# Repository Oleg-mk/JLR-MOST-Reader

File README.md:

# JLR MOST Reader

A listen-only adapter for the MOST25 optical ring in Jaguar and Land Rover cars. It takes the stereo
the head unit sends to the factory amplifier and outputs it as S/PDIF on a TOSLINK socket, for an
aftermarket DSP or amplifier. On MOST that audio travels round the ring in channels any node can
read, so the reader can hear exactly what the amplifier plays.
**The car's own volume knob and steering-wheel buttons keep working: the reader applies their level
digitally, with no loss of quality** ([how](#volume-from-the-cars-own-controls-with-no-loss-of-quality)).
It can also log everything it sees on the ring to a laptop over USB.

**Status, 2026-10-11: designed and verified in simulation, but never built and never tried in a
car.** The author can't build it locally, so the whole design is published here for anyone who can.
Every file you need to order, flash and assemble one is in this repository.

**This is a research project.** Every finding, recording, correction or bit of help is welcome
and will go into the project: open an issue or a pull request, or write in the forum thread.

Ukrainian: [README.uk.md](README.uk.md).

## Volume from the car's own controls, with no loss of quality

The audio on the ring travels before the volume: the factory amplifier applies volume and tone
itself. A plain MOST-to-TOSLINK tap would therefore play at full level, whatever the knob says.
The reader decodes the volume messages and applies the level itself, in the digital domain.

- **The stock controls keep working.** The knob and the steering-wheel buttons set the level as
  before. Navigation prompts and phone calls are mixed in at their own levels, and a Mute
  (0x22.0x113) is applied.
- **Nothing is lost on the way:**
  - the 16-bit stereo is taken straight from the ring's frames, sample for sample;
  - the level is applied in 32-bit arithmetic (a 72-bit accumulator) and rounded once, to the
    24-bit output. Every bit of the 16-bit source survives down to 48 dB of attenuation, and the
    rounding sits at the 24-bit level, about 144 dB below full scale;
  - no resampling: the S/PDIF runs at the ring's own 48 kHz, one output frame per ring frame;
  - no DAC or ADC in between: the sound stays digital until your DSP or amplifier.
- **Level changes are smooth:** a new level settles in about 5 ms, without clicks.

Your DSP or amplifier can then run at a fixed gain, and the car's controls do the rest. One thing
is still open: if the XF's amplifier turns out to get the gateway's 0x409 levels rather than
SpeakerLevel in dB, their raw-to-dB curve has to be measured from a recording (see
[Status](#status-what-is-proved-and-what-is-not)).

## What it does

- **Not an amplifier emulator.** An emulator takes the factory amplifier's place on the ring and
  answers the head unit as the amplifier. This reader takes no place on the network: the factory
  amplifier stays in the ring and keeps working, and the reader reads the same audio channels the
  amplifier plays and processes them. In effect it is a MOST bus sniffer with an audio path.
- **Sits in the ring like any MOST device:** fibre in, fibre out. A loop-in adapter cable opens the
  ring at an existing node's connector.
- **Decodes the control channel:** Connect and DisConnect to the amplifier (FBlock 0x22
  AudioAmplifier; on the XF node 0x186, instance 0x05, but any node and instance is taken, see
  [Status](#status-what-is-proved-and-what-is-not)), SinkInfo, Mute, and the two volume messages
  seen so far (0x22.0x46D SpeakerLevel in dB, and the gateway's 0xF0.0x409 levels).
- **Plays four streams from the frames,** at the positions the Connect messages give: the main
  source; phone, navigation and voice prompts; the parking sensors; the chimes. These are the
  amplifier's sinks 1 to 4 as JLR uses them. Each stream gets its own level and mute: the
  parking sensors follow their own level setting, and the chimes keep a fixed level, so they can't
  disappear with the volume turned down.
- **Outputs S/PDIF:** 24-bit, at the ring's 48 kHz, IEC 60958-3 consumer format, through an
  Everlight T10 TOSLINK transmitter.
- **Logs to a laptop:** what it receives and what it decides, through the Tang Nano's USB-UART.
  The laptop tools (Python, Windows 10/11 and macOS) record a drive and decode it at home.
- **Never transmits on MOST** and has no address.

Hardware: a Sipeed Tang Nano 20K FPGA module (GW2AR-18) on a small carrier board, with a TE MOST FOT
header, power from the car's permanent 12 V (KL30), and a TOSLINK transmitter. The gateware runs on
one clock and replaces both the MOST chip and the host CPU that a design like this usually needs.

## Which cars

- **Target:** Jaguar XF X250 (2008-2015). The messages it decodes are the ones open projects
  recorded on JLR cars (see [SOURCES.md](SOURCES.md)).
- **What the car must have:** a MOST25 ring at 48 kHz, and a separate amplifier that gets its audio
  over that ring. The amplifier stays in place: the head unit sends the audio to it, and the reader
  finds that audio from the Connect messages addressed to the amplifier.
- **Not the standard audio.** In cars where the head unit's own amplifier drives the speakers (the
  XF's standard audio), no audio for an amplifier travels the ring, so the reader has nothing to
  take. Switching the car's configuration from premium to standard stops that audio (a forum
  member with SDD), and mObridge's guide asks for the car to be coded when the factory MOST
  amplifier is missing ([SOURCES.md](SOURCES.md)).
- **Other cars:** other JLR models of the same generation with the same setup are candidates;
  Freelander 2 is the one with published evidence. Volume messages differ between models, and the
  logger exists to find that out.
- **Not other makes:** the Audi and BMW systems surveyed run their rings at 44.1 kHz and use
  different control messages.

## Is it safe for the car's ring?

The part that stays in the ring is small and separate from everything else:

```
ring in -> FOT receiver -> R1 -> U1 (one 74LVC1G34 buffer) -> R2 -> FOT transmitter -> ring out
```

- **The bypass:** U1 and the FOT run from their own 3.3 V regulator (TPS7B8133). It is fed from
  KL30 through the board's 12 V input (the fuse F1, the diode D1, the filter L2) and is always on,
  drawing tens of microamps with the car parked (the design figure; not yet measured). Nothing
  switches this path. It drives the transmitter the same way a powered OS8104 node in all-bypass
  does after reset.
- **Everything else is off the light path:** the FPGA module, its 5 V buck converter (switched on
  by light arriving on the ring), the gateware and the TOSLINK output. If the module, the gateware
  or the output fails, the ring still passes light. The FPGA's input is isolated by a 74LVC1G125
  with Ioff, so an unpowered module doesn't load the line.
- **When the ring opens:**
  - the bypass loses its supply: KL30 disconnected, or your fuse or F1 blown;
  - a part on the board's 12 V input fails: the bypass shares that input with the buck, so a
    short there (the buck's input, a capacitor on the 12 V side, D2) blows F1, and an open F1, D1
    or L2 cuts the supply;
  - a part on the light path fails: J1's FOT, R1, U1, R2 (and R43 on v2.0), or the 3.3 V
    regulator.

  The same is true of every factory MOST node that loses its supply. Fit your own fuse where you
  tap KL30.
- **Nothing new on the network:** the reader sends nothing on MOST and has no address, so the car's
  network sees no new node.
- **Fully reversible:** unplug the loop-in adapter and the car is back to stock.
- **Start-up volume:** until the first volume message arrives, the main source plays at -12 dB, and
  phone/navigation, the parking sensors and the chimes at -6 dB. Keep your DSP's or amplifier's own gain low on the
  first drive.

## The factory amplifier

The reader only listens, so the factory amplifier stays in the ring, powered, and keeps playing.
That is the price of not emulating it, and it decides how you use the output.

- **Add to the stock system:** a subwoofer, a second amplifier, a DSP for extra speakers. Nothing
  in the car changes.
- **Take the factory speakers over:** your amplifier, fed by the reader, drives the factory
  speakers, and the factory amplifier is left without them.
  - **Fault codes:** it tests its speaker lines, so expect speaker-open codes in it. An XKR owner
    who did exactly this with a commercial MOST interface reports codes for the amplifier and
    every speaker that come back after clearing ([SOURCES.md](SOURCES.md)).
  - **Anything beyond the codes** is still being looked into. Findings are welcome.
  - **The service sounds:** per mObridge's guide, JLR sends the phone, navigation and voice prompts
    (sink 2), the parking sensors (sink 3) and the chimes (sink 4) to the amplifier over the ring
    as audio. The reader plays all of them, so moving the speakers loses none. The first
    recording will confirm it: the trip instructions ask for a mark at reverse gear and at every
    chime.

**Can the reader replace the factory amplifier? No.**
- **Nobody answers for it.** The reader has no address and sends nothing, by hardware: the ring's
  transmitter is driven by one buffer, and the FPGA has no way onto it. With the amplifier gone,
  nobody answers as node 0x186 / FBlock 0x22.
- **The car needs it.** An XF owner who bypassed the amplifier with a fibre loop reports the screen
  stuck on the logo and no sound ([SOURCES.md](SOURCES.md)).
- **That is an emulator's job.** Taking the amplifier's place means transmitting on MOST.
- **It must stay powered.** Without power its own bypass goes dark and the ring opens.

## Status: what is proved and what is not

**Verified in models** (run `python check_all.py`; every step passes):

- The gateware, in Icarus Verilog against bit-exact Python models:
  - the control decoder, through five scenarios and 400 random blocks;
  - the frame timing at +-1000 ppm with jitter;
  - the DSP and the S/PDIF line, read back and decoded;
  - the whole reader from the optical line: a modelled JLR ring distorted to the edge of the MOST25
    receiver limits (SP4), through to the S/PDIF output;
  - the ring log, record by record, as far as the laptop's parser.
- The Gowin build meets timing with at least 10 % margin; the bitstream in `kit/2_fpga` was built
  from the committed sources.
- The boards:
  - KiCad ERC and DRC clean, with parity between schematic and board;
  - the v2.0 netlist compared with v1.0 part by part and net by net;
  - the board's fit in the tube and the end caps, all generated from one model (`reader_hw2/check_fit.py`).
- The decoder and the gain tables, cross-checked against C code written separately in the author's
  earlier project, [MOST25-to-AUDIO](https://github.com/Oleg-mk/MOST25-to-AUDIO).

**Unknown until a bench or a car:**

- **Volume message:** which one the XF's amplifier actually gets. Both are decoded. JLR-HU's
  table of the amplifier's own functions lists 0x46D SpeakerLevel and not 0x400 Volume: a point
  for 0x46D.
- **Connect:** whether the stock head unit sends 0x22.0x111 Connect at all.
- **The 0x409 levels:** JLR-HU's author has read them two ways; the later one is used (the volume
  in byte 2, the navigation in byte 9, the parking sensors in byte 11). The level curves are
  placeholders.
- **Mute:** whether JLR mutes with 0x113 Mute, which is decoded, or with 0x466 MuteParameters,
  which is not (usb2most's firmware mutes with 0x466).
- **MixerLevel:** 0x22.0x467 is not decoded. It is not among the amplifier's own functions in
  JLR-HU's table and is taken to belong to the gateway's shadow amplifier (below).
- **The gateway's shadow amplifier,** 0x22 instance 0xA1 at node 0x161: the reader does not tell
  it apart from the amplifier, so a Connect or a Mute sent to it would act on the reader's streams.
- **Real hardware:** how a real S/PDIF receiver locks to the output's edges, which sit on a
  1.26 ns grid, and whether the module's USB bridge sustains 3 Mbaud into Windows.

The log is designed to answer these on the first drive ([reader_gw/README.md](reader_gw/README.md),
[reader_gw/LOGGING.md](reader_gw/LOGGING.md)).

## Build one

The short version is below; the full guide is [BUILD.md](BUILD.md). There are two boards with the
same circuit. **v2.0** (`reader_hw2/`) is the one to build:
84.9 x 26.5 mm, two layers, inside a 30 x 30 x 1.5 mm aluminium tube with two 3D-printed end caps.
v1.0 (`reader_hw/`) is a flat 77.5 x 55.6 mm board with mounting holes.

1. **Measure first.** The end caps depend on the tube's inside (27.0 mm nominal), how far the
   module's HDMI and USB-C stick out past its board (4 and 2 mm assumed), and J4's tail length
   (3.0 mm assumed). The list is in `reader_hw2/kit/1_boards/README.md`, "Перед замовленням виміряти".
2. **Order the boards** from JLCPCB. Everything is in `reader_hw2/fab/`.
   - Board: `most_reader_v2-gerbers.zip`. 2 layers, 1.6 mm, 1 oz, ENIG; U4, U5 and U6 need flat pads.
   - Assembly: the bottom side only, with `most_reader_v2-bom-jlcpcb.csv` and
     `most_reader_v2-cpl-jlcpcb.csv`. That is 30 lines and 52 parts, every one with its LCSC number.
   - In their placement preview, check pin 1 of U1, U3, U4, U5 and U6, and the polarity of D1, D2,
     D3, C44, C45 and C63.
3. **Buy the hand-soldered parts:**

   | Ref | Part | Note |
   |---|---|---|
   | J1 | TE 1-1394640-1, MOST pigtail FOT header (2+0) | not stocked by Mouser or DigiKey; marketplaces only, look early |
   | J4 | Molex 43650-0200, Micro-Fit 3.0 right angle; mating 43645-0200 and two 43030 terminals | 12 V from KL30 |
   | J6 | Everlight PLT237/T10WH | DigiKey 1080-PLT237/T10WH-ND |
   | M1 | Sipeed Tang Nano 20K | with its pin headers, cut to nine pins |

   You also need:
   - a 30 x 30 x 1.5 aluminium tube, 84.9 mm (+0.2/-0) long, best left bare;
   - two M2 x 6 self-tapping screws, an M2 ring terminal and a serrated washer for the tube's ground;
   - four 4.2 mm self-tapping screws (DIN 7981) or M4 screws to fix it in the car;
   - a MOST loop-in adapter for the node you will tap, as made by Kufatec, Dension or Trioma;
   - a TOSLINK cable.
4. **Flash the FPGA** before soldering the module: write `kit/2_fpga/reader.fs` to its flash. On
   Windows use Gowin Programmer; on macOS, `openFPGALoader -b tangnano20k -f --verify reader.fs`.
   The module's BL616 bridge needs firmware 2025030317 or newer (`kit/2_fpga/README.md`).
5. **Solder:**
   - J6 and J4 from below, with their leads cut flush where the module will sit;
   - J1 on top at the ring edge;
   - M1 last, on nine header pins only: 5, 7, 8, 20 and 21, 22, 25, 35, 40. Cut the strips into
     pieces (5 | 7-8 | 20 and 21-22 | 25 | 35 | 40) and let the board hold them square.
6. **Bench:**
   - Check for shorts across J4, C3 and C63, then power from a current-limited 12 V supply.
     C3 shows 3.3 V at all times.
   - With light into J1, C63 shows about 5.3 V and the module starts.
   - Then record on the bench with the laptop tools (`kit/3_laptop/`).
7. **Tube:**
   - Print the caps from `reader_hw2/caps/` in PETG or ASA. The drawing is
     [caps_en.svg](reader_hw2/caps/caps_en.svg).
   - Fit the far cap, slide the board in from the ring end until it meets the far cap, then fit
     the ring cap; one screw each.
   - Run a short wire from the far cap's screw to J4's ground at the plug.
   - Each cap runs on under the tube into a saddle with an ear on either side. The tube's floor
     rests on the two saddles, and four screws through the ears hold the reader in the car.
8. **Car:**
   - First the bypass alone: the reader in the ring, powered, and the car must sound exactly as before.
   - Then a drive with the log running.

**The full step-by-step guide in English is [BUILD.md](BUILD.md).** The same instructions in
Ukrainian are the kit's: [reader_hw2/kit/README.md](reader_hw2/kit/README.md),
[reader_hw2/kit/1_boards/README.md](reader_hw2/kit/1_boards/README.md),
[kit/2_fpga/README.md](kit/2_fpga/README.md) and [kit/3_laptop/README.md](kit/3_laptop/README.md).
The board and its design choices are described in [reader_hw2/README.md](reader_hw2/README.md).

## Rough cost

| Item | Approx. USD | Basis |
|---|---|---|
| JLCPCB: 5 boards, 2 of them assembled | 60-100, plus shipping and tax | their price page, seen 2026-10-12 (updated 2026-09-09): Economic PCBA (one side, as here): $8.18 setup, $1.53 stencil and $3.07 per extended part type (about 15 here), plus the parts and the ENIG boards |
| Sipeed Tang Nano 20K | 25-35 | $25 at launch; resellers $27-36 |
| TE 1-1394640-1 (J1) | 22-27, plus shipping | no distributor stocks it; eBay about $22 (2026-10-12), AliExpress about $27 (2026-10-13) |
| T10 transmitter, Micro-Fit pair, tube, printed caps, screws, a fuse and wire for the 12 V tap | 15-25 | rough |
| MOST loop-in adapter, TOSLINK cable | 25-60 | rough; depends on the node you tap |

The first reader comes to roughly $150-250, plus shipping and tax. A second reader from the same
order needs no new boards: about $90-150 for its module, J1, the other hand parts, the tube and
the cables.

## Repository map

| Path | What |
|---|---|
| `reader_hw2/` | **v2.0 board** (KiCad 10): generators, the board, `fab/` for JLCPCB, `caps/` for the tube, `views/` pictures, `kit/` instructions |
| `reader_hw/` | v1.0 board, same circuit, flat with mounting holes |
| `reader_gw/` | gateware for the Tang Nano 20K: RTL, simulations, the Gowin build |
| `kit/` | what a builder takes away: v1.0 fab files, the bitstream, the laptop tools |
| `virtual_most_source/` | a Python model of a MOST25 ring and of JLR's messages, which the simulations use |
| `tools/` | checks: sheet, board, pins, cross-checks, the kit's builder, the laptop's logger and decoder |
| `check_all.py` | every check in turn |

Tools: KiCad 10, Python 3, OSS CAD Suite (Icarus Verilog) for the simulations, and Gowin EDA
1.9.12.03 to rebuild the bitstream (the committed one is ready to flash). Two cross-check steps
need the author's earlier project, [MOST25-to-AUDIO](https://github.com/Oleg-mk/MOST25-to-AUDIO),
cloned next to this one, and a host gcc; without them they fail ([SOURCES.md](SOURCES.md)).

## Licence

Copyright 2026 Oleg-mk.

- **Hardware, under CERN-OHL-S-2.0** ([LICENSE](LICENSE)):
  - `reader_hw/`, `reader_hw2/` (the KiCad design and the scripts that generate it, footprints,
    3D models, fabrication files, end caps);
  - the gateware in `reader_gw/rtl/` and `reader_gw/board/`;
  - `kit/1_boards/` and `kit/2_fpga/`.
- **Software, under GPL-3.0-or-later** ([COPYING](COPYING)):
  `virtual_most_source/`, `tools/`, `reader_gw/sim/`, `kit/3_laptop/` and `check_all.py`.
- **Documentation:** each README and drawing is under the licence of the directory it sits in.

If you build or change the hardware and share it, share your sources under the same licence.

## How it was made

The author made the decisions and placed the parts. Claude (Anthropic's AI model,
in Claude Code) wrote the gateware, the models and simulations, the board generators and copper,
and the checks, as a co-author. The commit history shows both.

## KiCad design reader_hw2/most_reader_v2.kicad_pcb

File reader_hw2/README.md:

# reader_hw2 - reader v2.0: v1.0's circuit plus two resistors, a board for a tube

v2.0 is v1.0's electronics, plus two series resistors (R43, R44, below) and a smaller C45, on a board that slides
into a square aluminium tube with two end caps: a 30x30x1.5 tube (27.0 inside), a board 26.5 mm
wide, the module's own USB-C in the far end cap with no extension cable. v1.0 (`reader_hw`) is
not touched.

```text
python reader_hw2/gen_reader2.py               the sheet, the libraries, the footprints, the 3D bodies
"%LOCALAPPDATA%\Programs\KiCad\10.0\bin\python.exe" reader_hw2\gen_reader2_pcb.py [--fresh]
                                               the first placement (refuses to overwrite without --fresh)
"%LOCALAPPDATA%\Programs\KiCad\10.0\bin\python.exe" reader_hw2\check_fit.py
                                               the board in the tube: heights, corners, leads, the caps
python tools/check_v2_circuit.py               v2.0's circuit equals v1.0's once R43, R44 are shorted
python tools/check_board.py reader_hw2/most_reader_v2.kicad_pcb
                                               DRC with the parity check, the silkscreen minimums
python reader_hw2/make_fab.py                  the manufacturing package in fab/: JLCPCB, SMD on the bottom
"%LOCALAPPDATA%\Programs\KiCad\10.0\bin\python.exe" reader_hw2\gen_caps.py
                                               the tube's end caps in caps/: STEP, STL, the drawing
python tools/make_kit.py --v2 DIR              the kit in DIR: 1_boards, 2_fpga, 3_laptop (READMEs in kit/)
```

All but the last run in `check_all.py`.

## The sheet

`gen_reader2.py` does not draw the circuit again: it loads `reader_hw/gen_reader.py` and writes
its blocks 1-7 into this folder, under the project name `most_reader_v2` with its own UUIDs. It
changes what describes the board and adds two resistors:

- the title block (rev 2.0) and two lines of notes;
- the Tang Nano footprint: nine pads only, 5, 7, 8, 20 and 21, 22, 25, 35, 40: the
  seven that carry something and one at each corner they leave bare. The strips are cut to them
  (pieces of one and two pins), and the rows of holes under the module are free for tracks; pins
  1..4 would sit over J4 on the other side anyway. KiCad's parity check asks no pad of an
  unconnected pin.
  The footprint also draws the module's real overhangs (USB-C 2 mm, HDMI about 4 mm; v1.0's fab
  text says 8 mm, which was never measured) and carries a 3D body of the module;
- the FOT footprint's two action pins: rings of 2.1 mm instead of 2.4, so that their copper keeps
  0.3 mm from the long edges of the 26.5 mm board (their 1.8 mm holes sit 0.5 mm from them);
- R43 (33 ohm) and R44 (68 ohm) in series right after U1 (RX_BUF) and U3 (RX_IN): on two layers
  those lines run about 40 and 60 mm as 100-130 ohm lines with ~1 ns LVC edges. A model of RX_IN
  (the line, U3 at 15-25 ohm, the FPGA pin 6-8 pF) gives 13-31 % overshoot with 33 ohm and at
  most 8 % with 68, the edge 1.0-1.6 ns, which the decoder does not mind. R43 stays 33: RX_BUF
  also drives the ring's TX through R2, where a fast edge matters more.
- C45 47u 63V in 8 x 10 instead of 100u in 10 x 10.5. The bulk capacitance on
  VBAT_P drops from 200 to 147 uF, 9.6 times the 15.3 uF of ceramics there (13 before): still
  enough to damp the harness against them.

`tools/check_v2_circuit.py` compares both sheets' netlists with R43 and R44 shorted out and C45's
one change allowed: 58 parts, 63 nets, no other difference.
Since `tools/check_pins.py` holds v1.0's sheet to the gateware's `.cst`, the gateware and the
bitstream in `kit/2_fpga` hold for v2.0 unchanged.

## Why 26.5 mm and 1.5 mm walls

Both come from J1, not from the module:

- **Width.** J1's housing is 25.5 mm wide (TE's view drawing C-2-2141577-1), and its two action
  pins stand in 1.8 mm holes whose outer edges are 25.5 mm apart. A 26 mm board would leave
  0.25 mm of FR-4 outside each hole.
- **Height.** J1 stands 13.25 mm above the board, more than the module's 10.1. With the board and
  C44 underneath (10.5 + 0.3): 13.25 + 1.6 + 10.8 = 25.65 mm. A 2 mm wall (26 inside) leaves
  0.35 mm for everything; 1.5 mm (27 inside) leaves 1.35: 0.5 above J1, 0.5 under C44, and the
  window for the board's height.

## The layout

26.5 x 84.9 mm, two layers. x runs along the tube from the ring's end (0) to the far end (84.9).

| Side | Where | What |
|---|---|---|
| top | ring end | J1, its foot on the edge, its housing 3.6 mm past it |
| top | x 31..85 | M1 along the tube, its USB-C on the far edge (2 mm past it, into the cap's cut-out) |
| bottom | under J1, x 10..22 | the FOT's supply filters on J1's pins; U4 with its RC; R1, U1 and R43 at RXD, R2 at TXD |
| bottom | x 21..37 | U5 with C46 and C3 behind J1; the bulk capacitor C44 with C47; U3 and R44 (/WAKE between its pads) |
| bottom | x 34..58 | U6 with C4, C82, C2, R31, C6 and the divider R4, R5; L1 and C7 for 5V_SW; C45, C43, C1, C84 on the VBAT_P bus |
| bottom | x 54..76 | the input from J4: L2, D1, D2, F1, C83; at the module's 5 V pin C63, C85, D3; R28, C31, C32 for J6 |
| bottom | far end | J4 (power) under the module's pins 1..4, J6 (TOSLINK) beside it |

Nothing but J1 and M1 is on top: the module's own parts (DC-DC, LDOs, crystals, the microSD slot)
fill the 2.5 mm under it.

Two lines run long, each from a buffer through a series resistor right after it: RX_IN from U3
through R44 (68 ohm) to the FPGA's pin 27 (module pad 8), 40 mm, and RX_BUF from U1 through R43
(33 ohm) to U3, R2 and U4, 20, 29 and 32 mm. VBAT_P comes from J4 through L2 along the bus at y 11
(C1, C43, C45) to U6's input caps and on to C44 and U5; /WAKE runs from U4 to U6, 3V3_SW from pad 7
to J6 and back along the bottom edge to U3.

**The length.** 84.9 mm. The module's end stays on the far edge, its HDMI 5.65 mm clear of J1.

## The model: check_fit.py

Every part is a box: its courtyard on the board and its height from a table with the source of
each number. The checks:

1. the board in the tube, at least 0.2 mm a side (0.25 now);
2. the tallest part on top plus the board plus the tallest underneath, with 0.5 mm above and
   below: the board's underside may sit 11.30..11.65 mm above the tube's floor, and goes at 11.47
   (the caps' slot); a tube 0.35 mm smaller inside still fits;
3. no box corner outside the tube's inside with its corners rounded by up to 1.0 mm (J1's housing
   is 1.10 and 0.40 mm from the walls, 0.68 under the top);
4. leads: J1's pins, legs and pegs land on no part underneath; no part underneath covers a pad
   of the module's header (its pins are soldered from underneath); J6's and J4's leads do not
   come up under J1 (it sits 0.45 mm above the board); under the module they are listed, to be
   cut flush;
5. the ends, with caps 2.0 mm thick: J1's housing 1.6 mm out of the ring cap; the USB-C's face on
   the far cap's outer face (0.06 inside); J6's port 0.29 out; J4's face 2.06 inside; the HDMI
   5.65 mm clear of J1.

It prints the caps' cut-outs (y from the left inside wall as seen from outside that end, z from
the tube's floor, mm), today:

| Cap | Cut-out | y | z |
|---|---|---|---|
| ring | J1's housing | 1.10..26.60 | 13.52..26.32 (the port sleeve's axis 19.92) |
| far | USB-C centre (receptacle 8.94 x 3.26) | 13.50 | 18.80 |
| far | J6's port axis | 9.50 | 7.12 |
| far | J4's face | 15.25..24.85 | 5.40..11.47 |

Planted faults (C44 over J1's peg, a part over a header pad, J6 under J1) each fail the check.

## Before the boards are ordered: measure

The model's weak numbers, in the order they matter:

- the tube's inside (27.0 nominal) and its corner radius;
- the module: how far the HDMI and the USB-C stand past its PCB, and the tallest part on its
  underside near the USB-C end (J6's and J4's cut leads sit there; 2.0 mm assumed);
- J4's tail and peg length under its seating plane (3.0 assumed);
- the caps' thickness at the cut-outs (2.0 assumed): the module's USB-C must end on the far cap's
  outer face.

## Assembly

1. JLCPCB places every SMD part, on the bottom.
2. J6 and J4 from the bottom, soldered on top; their leads (and J4's peg) cut flush where the
   module will sit.
3. J1 on top, soldered underneath.
4. The module on nine pins: the strips cut into pieces (5 | 7-8 | 20 and 21-22 | 25 | 35 | 40),
   put into the board, the module on top, soldered to the module first (the board holds them
   square), then underneath.

## Routing by hand

The board file is the master: `gen_reader2_pcb.py --fresh` would throw the copper away. The top is
the ground plane; underneath:

- the power section: C6 between U6 and L1, the SW node 3.7 mm, C4 straight onto U6's VIN and
  exposed pad; C45 8 mm across, on the bus by U6;
- the module's header cut to nine pins; the freed rows carry RX_IN and 3V3_SW;
- the far end: D3 lying, SPDIF between its pads; 3V3_SW from pin 7 between F1's and R28's pads to
  C31, C32 and J6, and from J6 down to the line under the module;
- /WAKE and RX_BUF straight across, from the top edge to their runs at x 25.5 and 25.05.

496 mm of copper, 75 vias; on the top only two jumpers, RX_IN over the C44 link (1.65 mm) and
VBAT_P over RX_BUF and /WAKE (1.75 mm); the top pour in one piece. DRC 0, no difference from the
sheet, nothing unconnected; no track runs over a pad of its own net without ending in it, no via
sits in a pad, no bend is acute. The series resistors' value depends on the line's impedance, not
on its length.

The sheet's test points TP6, TP7, TP9, TP10 are not on the board; the kit measures on C3
(3V3_AON), C63 (5V_SW) and the module's pin 7 (3V3_SW).

## The manufacturing package and the kit

`make_fab.py` writes `fab/` with v1.0's code: the Gerbers (the bottom paste, both silkscreens), the
BOMs and JLCPCB's CPL for the bottom side, the schematic and two assembly drawings (the bottom seen
from below, the top). A bottom part's rotation for JLCPCB is the angle at which it is seen from
below, 180 minus KiCad's, plus the part's own turn from v1.0's table; checked against the pads of
all 52 parts. `tools/make_kit.py --v2 DIR` writes the kit: 1_boards from `fab/` with the README in
`kit/1_boards`, the README in `kit/`, and v1.0's 2_fpga and 3_laptop.

## The end caps: gen_caps.py

The caps come from `check_fit.py`'s model (it must pass) and the board's leads, into `caps/`: a STEP
and an STL of each (the print's frame: the outer face on the bed), `caps.svg` (each cap seen from
outside, in section and from below, the sizes, the notes; `caps_en.svg` the same in English) and a
README.

- A flange of the tube's outline, 30 mm square and 2.0 mm thick, sits on the tube's end face; the
  board's ends butt against the flanges, so the tube is 84.9 mm (+0.2/-0), as long as the board.
- Every opening is its part plus 0.25 mm a side; no wall is thinner than 1.2 mm (three lines of a
  0.4 mm nozzle). J6's body and J4's face share one opening: the web between two would be 0.4 mm.
- The ring cap's block carries the board's underside at 11.47 mm and ends 1.0 mm before the first
  part underneath (8.5 mm into the tube); it stays 2.0 mm off J1's soldered action pins, and a slot
  along it, open to the inside, lets J1's peg through while the cap slides on under the board.
- The far cap's block sits over the module's end, 0.5 mm above the USB-C.
- Under the tube each flange runs on into a saddle:
  3.0 mm thick, 9.0 mm along the tube from its end, an ear 10.0 mm out on either side with a 4.2 mm
  hole. The tube's floor rests on the two saddles, and four screws through the ears hold the reader
  in the car: 4.2 mm self-tapping (DIN 7981) or M4, a head up to 8.2 mm clears the tube's side. The
  ring cap's saddle has a 5.0 mm hole round the head of the cap's own screw.
  - A tab past the tube's end would lie below the bed with the cap printed outer
    face down, and would need the cap on its side with supports under both blocks. At the far end it
    would also pass about 1 mm under a TOSLINK plug (J6's port axis 8.6 mm above the tube's bottom,
    a plug about 10 mm tall). The saddle rises from the bed with the flange: no supports, the ear
    holes horizontal.
- Each cap takes a self-tapping M2 screw through the tube's wall into its block, the hole in the
  block drilled at assembly: through the floor at the ring end, through the top at the far end.
- The tube is bonded to ground by J4 through the far cap's screw: an M2 ring terminal and a
  serrated washer under its head, a 3-5 cm wire to the GND wire of J4's harness by the plug. The
  board has no room for a bond there: the module's header rows run 2.2 mm from both long edges,
  J4 and J6 fill the end; the tube raw, or its anodizing scraped off under the washer.
- The script fails, writing nothing, when a wall comes out thinner, an opening closer to its part,
  a block onto a part or a lead, a saddle hole nearer an edge than 1.2 mm, or the mesh is open.
- `make_views.py` puts both caps and the tube on a copy of the board, point by point from the same
  solids, and renders the pictures in `views/` at basic quality: J1, the USB-C and J6 in their
  openings, the saddles under the tube.

## Not yet

The caps printed and tried on a real tube.

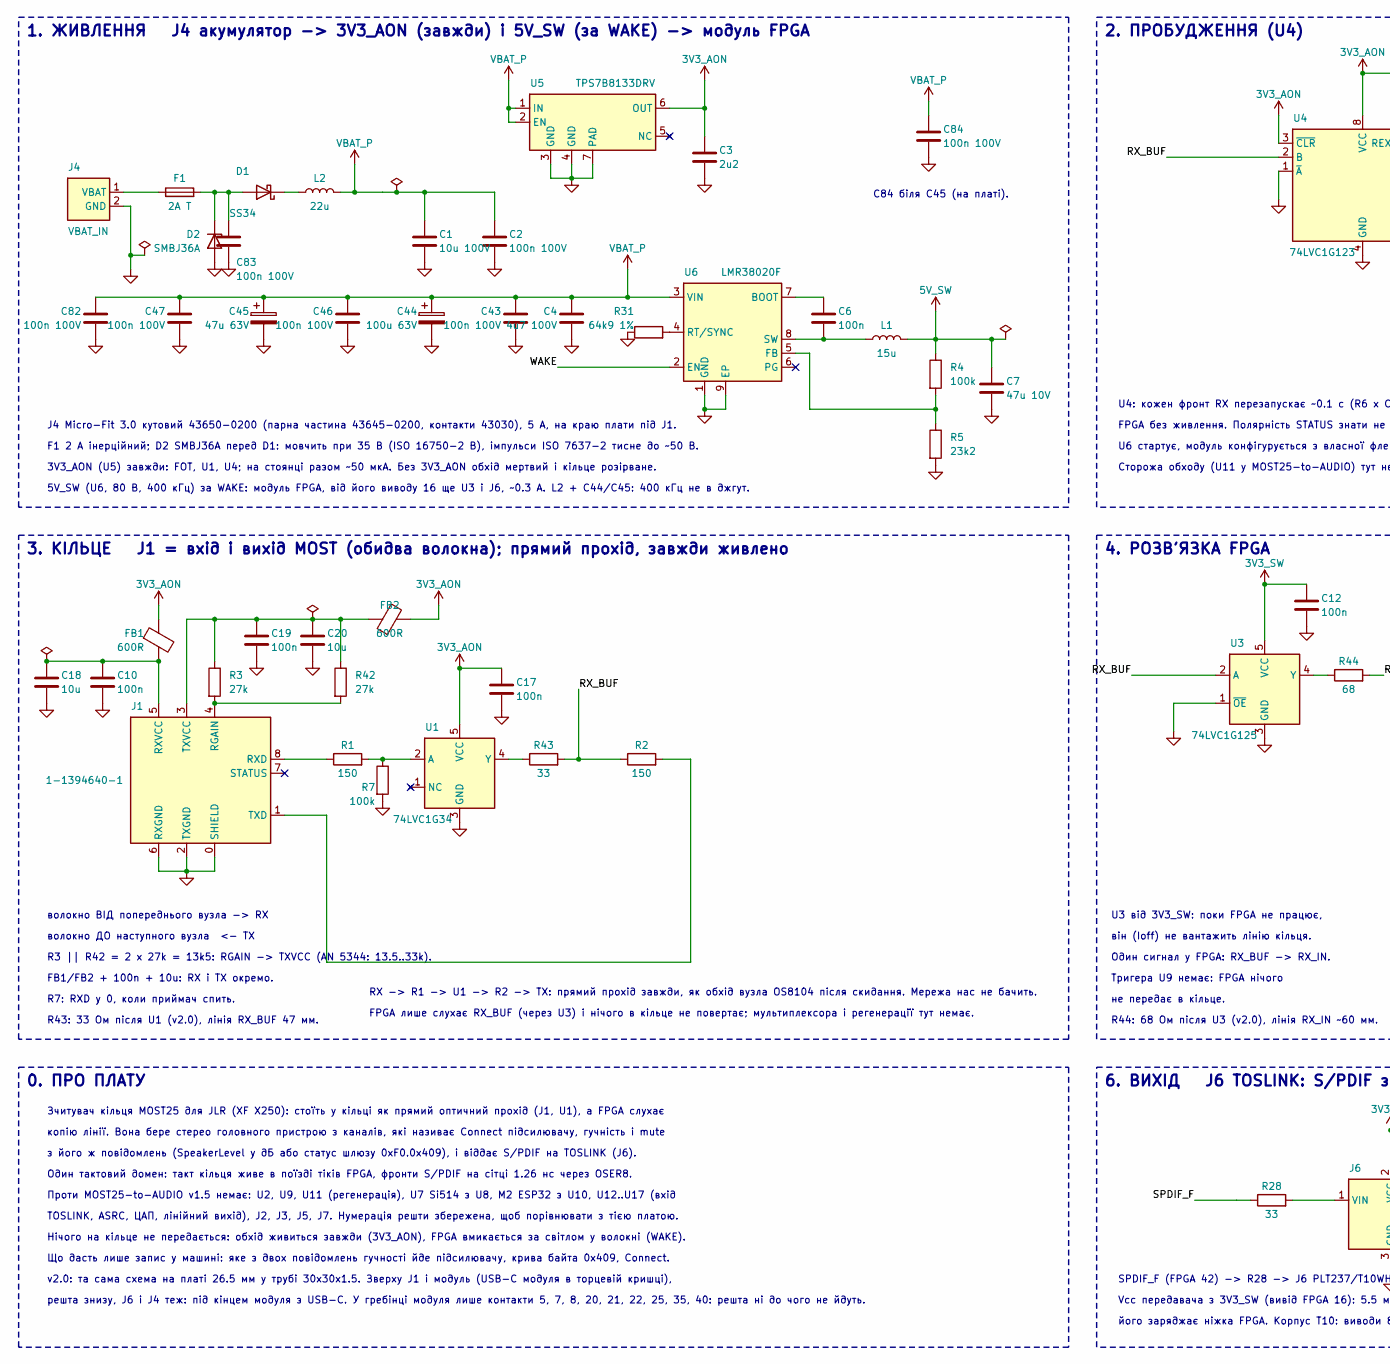
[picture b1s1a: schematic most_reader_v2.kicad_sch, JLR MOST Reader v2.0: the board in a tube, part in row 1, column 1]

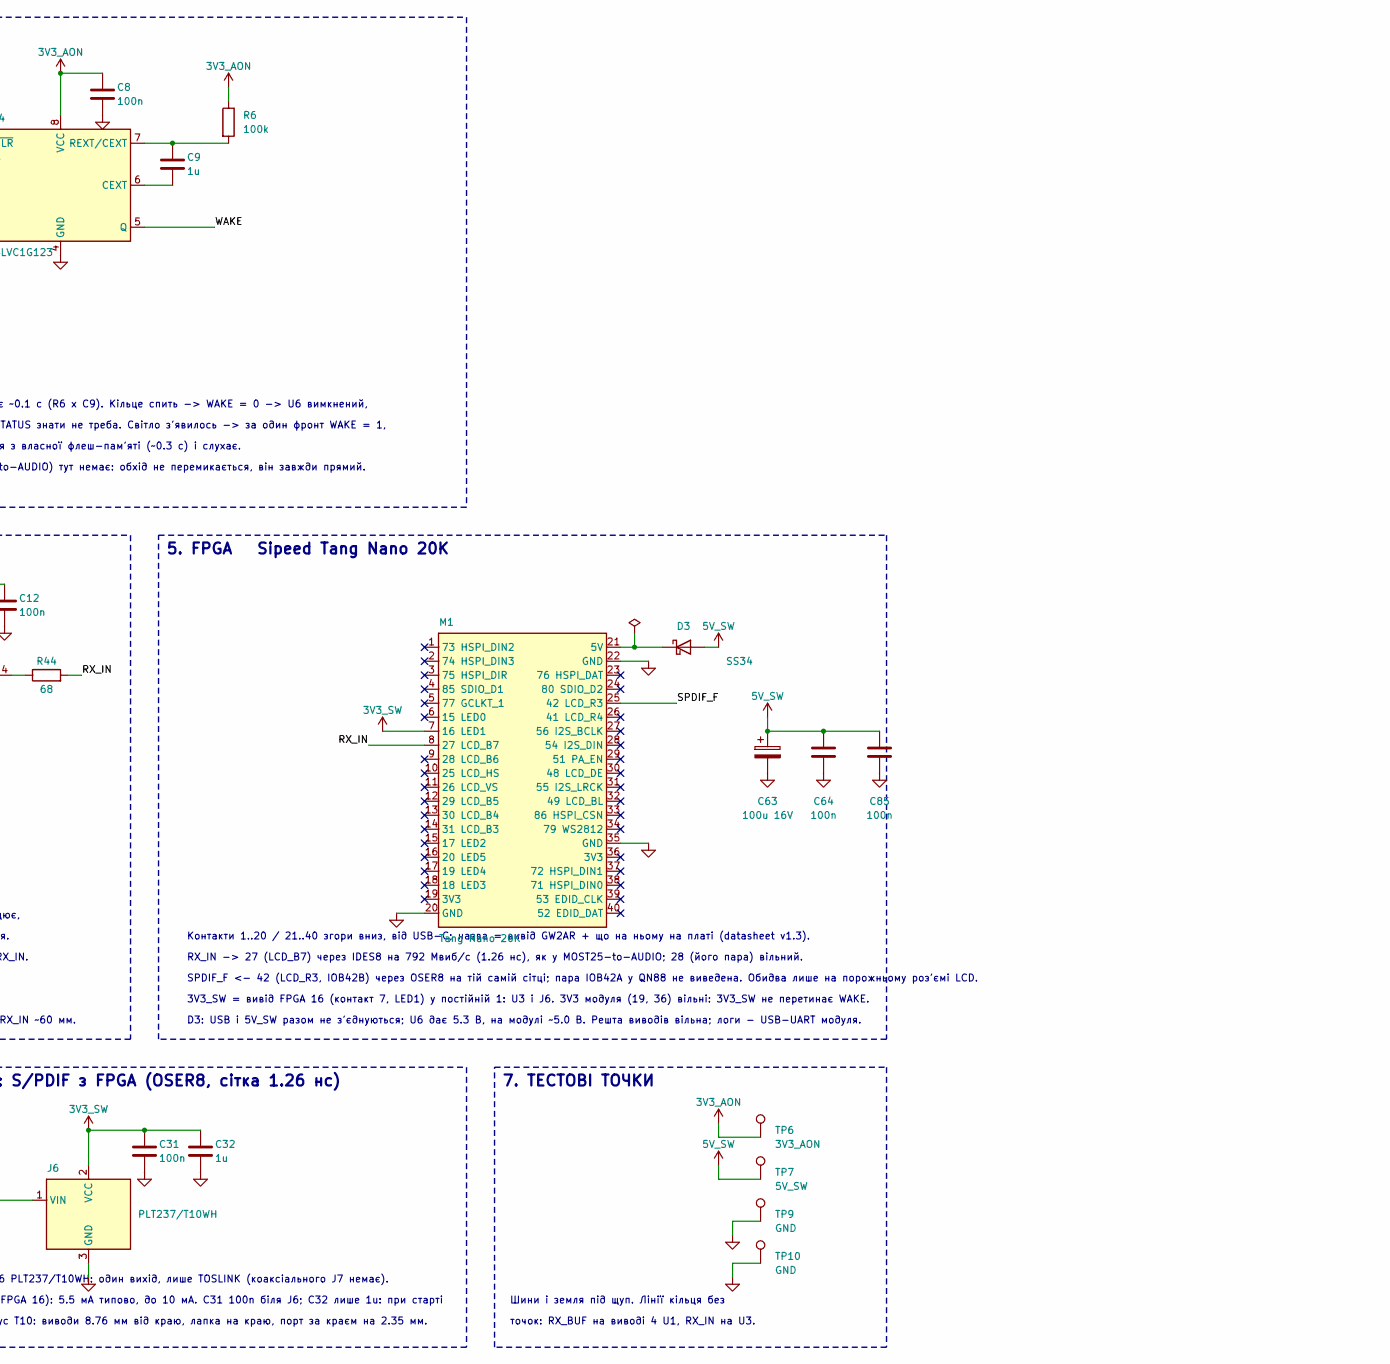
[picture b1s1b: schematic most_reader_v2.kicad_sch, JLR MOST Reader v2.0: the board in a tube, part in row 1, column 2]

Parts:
C1: 10u 100V; C_1210_3225Metric
C2, C43, C46, C47, C82, C83, C84: 100n 100V; C_0603_1608Metric
C3: 2u2; C_0603_1608Metric
C4: 4u7 100V; C_1210_3225Metric
C6, C8, C10, C12, C17, C19, C31, C64, C85: 100n; C_0603_1608Metric
C7: 47u 10V; C_1210_3225Metric
C9: 1u; C_0603_1608Metric
C18, C20: 10u; C_0805_2012Metric
C32: 1u; C_0805_2012Metric
C44: 100u 63V; CP_Elec_10x10.5
C45: 47u 63V; CP_Elec_8x10
C63: 100u 16V; CP_Elec_6.3x7.7
D1, D3: SS34; D_SMA
D2: SMBJ36A; D_SMB
F1: 2A T; Fuse_1206_3216Metric
FB1, FB2: 600R; L_0603_1608Metric
J1: 1-1394640-1; TE_MOST_Pigtail_FOT_2+0
J4: VBAT_IN; Molex_Micro-Fit_3.0_43650-0200_1x02_P3.00mm_Horizontal
J6: PLT237/T10WH; Everlight_TOSLINK_T10
L1: 15u; L_Bourns_SRN6045TA
L2: 22u; L_Bourns-SRN8040_8x8.15mm
M1: Tang Nano 20K; Sipeed_TangNano20K
R1, R2: 150; R_0603_1608Metric
R3, R42: 27k; R_0603_1608Metric
R4, R6, R7: 100k; R_0603_1608Metric
R5: 23k2; R_0603_1608Metric
R28, R43: 33; R_0603_1608Metric
R31: 64k9 1%; R_0603_1608Metric
R44: 68; R_0603_1608Metric
TP6: 3V3_AON; TestPoint_Pad_D2.0mm
TP7: 5V_SW; TestPoint_Pad_D2.0mm
TP9, TP10: GND; TestPoint_Pad_D2.0mm
U1: 74LVC1G34; SOT-353_SC-70-5
U3: 74LVC1G125; SOT-353_SC-70-5
U4: 74LVC1G123; VSSOP-8_2.3x2mm_P0.5mm
U5: TPS7B8133DRV; WSON-6-1EP_2x2mm_P0.65mm_EP1x1.6mm
U6: LMR38020F; Texas_HSOP-8-1EP_3.9x4.9mm_P1.27mm_ThermalVias

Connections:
3V3_AON: C3.1, C8.1, C17.1, FB1.1, FB2.2, R6.1, TP6.1, U1.5 (VCC), U4.3 (~CLR), U4.8 (VCC), U5.6 (OUT)
3V3_SW: C12.1, C31.1, C32.1, J6.2 (VCC), M1.7 (16 LED1), U3.5 (VCC)
5V_SW: C7.1, C63.1, C64.1, C85.1, D3.2 (A), L1.2, R4.1, TP7.1
/RX_BUF: R2.1, R43.2, U3.2 (A), U4.2 (B)
/RX_IN: M1.8 (27 LCD_B7), R44.2
/SPDIF_F: M1.25 (42 LCD_R3), R28.1
/WAKE: U4.5 (Q), U6.2 (EN)
GND: C1.2, C2.2, C3.2, C4.2, C7.2, C8.2, C10.2, C12.2, C17.2, C18.2, C19.2, C20.2, C31.2, C32.2, C43.2, C44.2, C45.2, C46.2, C47.2, C63.2, C64.2, C82.2, C83.2, C84.2, C85.2, D2.2 (A), J1.0 (SHIELD), J1.2 (TXGND), J1.6 (RXGND), J4.2 (GND), J6.3 (GND), M1.20 (GND), M1.22 (GND), M1.35 (GND), R5.2, R7.2, R31.1, TP9.1, TP10.1, U1.3 (GND), U3.1 (~OE), U3.3 (GND), U4.1 (~A), U4.4 (GND), U5.3 (GND), U5.4 (GND), U5.7 (PAD), U6.1 (GND), U6.9 (EP)
unnamed: C83.1, D1.2 (A), D2.1 (K), F1.2
unnamed: D1.1 (K), L2.1
unnamed: D3.1 (K), M1.21 (5V)
unnamed: J1.4 (RGAIN), R3.2, R42.2
unnamed: J1.8 (RXD), R1.1
unnamed: C10.1, C18.1, FB1.2, J1.5 (RXVCC)
unnamed: J1.1 (TXD), R2.2
unnamed: C19.1, C20.1, FB2.1, J1.3 (TXVCC), R3.1, R42.1
unnamed: F1.1, J4.1 (VBAT)
unnamed: J6.1 (VIN), R28.2
unnamed: R1.2, R7.1, U1.2 (A)
unnamed: R43.1, U1.4 (Y)
unnamed: R44.1, U3.4 (Y)
unnamed: C9.2, U4.6 (CEXT)
unnamed: C9.1, R6.2, U4.7 (REXT/CEXT)
unnamed: C6.1, U6.7 (BOOT)
unnamed: R4.2, R5.1, U6.5 (FB)
unnamed: R31.2, U6.4 (RT/SYNC)
unnamed: C6.2, L1.1, U6.8 (SW)
VBAT_P: C1.1, C2.1, C4.1, C43.1, C44.1, C45.1, C46.1, C47.1, C82.1, C84.1, L2.2, U5.1 (IN), U5.2 (EN), U6.3 (VIN)

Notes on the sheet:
1. ЖИВЛЕННЯ J4 акумулятор -> 3V3_AON (завжди) і 5V_SW (за WAKE) -> модуль FPGA
J4 Micro-Fit 3.0 кутовий 43650-0200 (парна частина 43645-0200, контакти 43030), 5 А, на краю плати під J1.
F1 2 А інерційний; D2 SMBJ36A перед D1: мовчить при 35 В (ISO 16750-2 B), імпульси ISO 7637-2 тисне до ~50 В.
3V3_AON (U5) завжди: FOT, U1, U4; на стоянці разом ~50 мкА. Без 3V3_AON обхід мертвий і кільце розірване.
5V_SW (U6, 80 В, 400 кГц) за WAKE: модуль FPGA, від його виводу 16 ще U3 і J6, ~0.3 А. L2 + C44/C45: 400 кГц не в джгут.
C84 біля C45 (на платі).
2. ПРОБУДЖЕННЯ (U4)
U4: кожен фронт RX перезапускає ~0.1 с (R6 x C9). Кільце спить -> WAKE = 0 -> U6 вимкнений,
FPGA без живлення. Полярність STATUS знати не треба. Світло з'явилось -> за один фронт WAKE = 1,
U6 стартує, модуль конфігурується з власної флеш-пам'яті (~0.3 с) і слухає.
Сторожа обходу (U11 у MOST25-to-AUDIO) тут немає: обхід не перемикається, він завжди прямий.
3. КІЛЬЦЕ J1 = вхід і вихід MOST (обидва волокна); прямий прохід, завжди живлено
волокно ВІД попереднього вузла -> RX
волокно ДО наступного вузла <- TX
RX -> R1 -> U1 -> R2 -> TX: прямий прохід завжди, як обхід вузла OS8104 після скидання. Мережа нас не бачить.
FPGA лише слухає RX_BUF (через U3) і нічого в кільце не повертає; мультиплексора і регенерації тут немає.
R3 || R42 = 2 x 27k = 13k5: RGAIN -> TXVCC (AN 5344: 13.5..33k).
FB1/FB2 + 100n + 10u: RX і TX окремо.
R7: RXD у 0, коли приймач спить.
R43: 33 Ом після U1 (v2.0), лінія RX_BUF 47 мм.
4. РОЗВ'ЯЗКА FPGA
U3 від 3V3_SW: поки FPGA не працює,
він (Ioff) не вантажить лінію кільця.
Один сигнал у FPGA: RX_BUF -> RX_IN.
Тригера U9 немає: FPGA нічого
не передає в кільце.
R44: 68 Ом після U3 (v2.0), лінія RX_IN ~60 мм.
5. FPGA Sipeed Tang Nano 20K
Контакти 1..20 / 21..40 згори вниз, від USB-C; назва = вивід GW2AR + що на ньому на платі (datasheet v1.3).
RX_IN -> 27 (LCD_B7) через IDES8 на 792 Мвиб/с (1.26 нс), як у MOST25-to-AUDIO; 28 (його пара) вільний.
SPDIF_F <- 42 (LCD_R3, IOB42B) через OSER8 на тій самій сітці; пара IOB42A у QN88 не виведена. Обидва лише на порожньому роз'ємі LCD.
3V3_SW = вивід FPGA 16 (контакт 7, LED1) у постійній 1: U3 і J6. 3V3 модуля (19, 36) вільні: 3V3_SW не перетинає WAKE.
D3: USB і 5V_SW разом не з'єднуються; U6 дає 5.3 В, на модулі ~5.0 В. Решта виводів вільна; логи - USB-UART модуля.
6. ВИХІД J6 TOSLINK: S/PDIF з FPGA (OSER8, сітка 1.26 нс)
SPDIF_F (FPGA 42) -> R28 -> J6 PLT237/T10WH: один вихід, лише TOSLINK (коаксіального J7 немає).
Vcc передавача з 3V3_SW (вивід FPGA 16): 5.5 мА типово, до 10 мА. C31 100n біля J6; C32 лише 1u: при старті
його заряджає ніжка FPGA. Корпус T10: виводи 8.76 мм від краю, лапка на краю, порт за краєм на 2.35 мм.
7. ТЕСТОВІ ТОЧКИ
Шини і земля під щуп. Лінії кільця без
точок: RX_BUF на виводі 4 U1, RX_IN на U3.

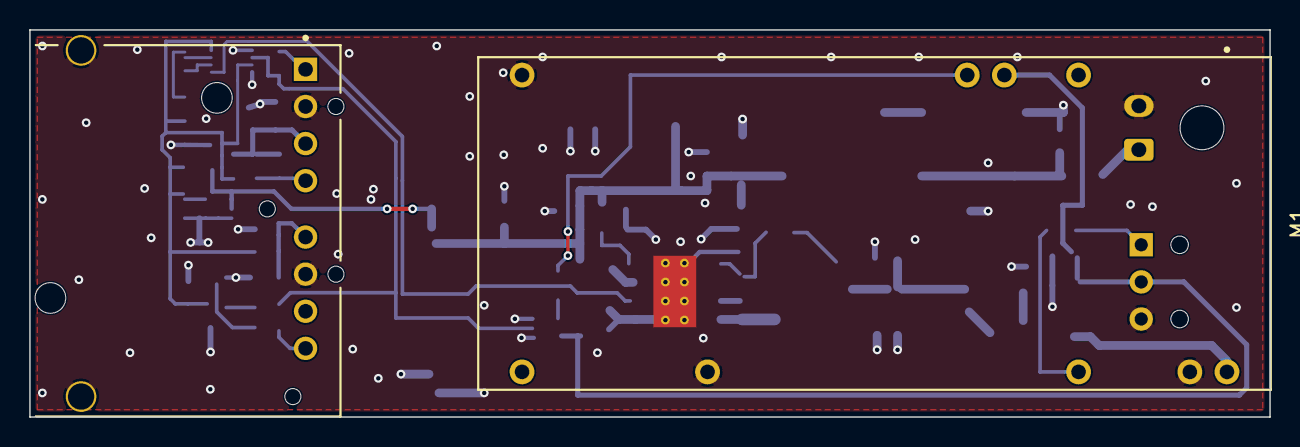
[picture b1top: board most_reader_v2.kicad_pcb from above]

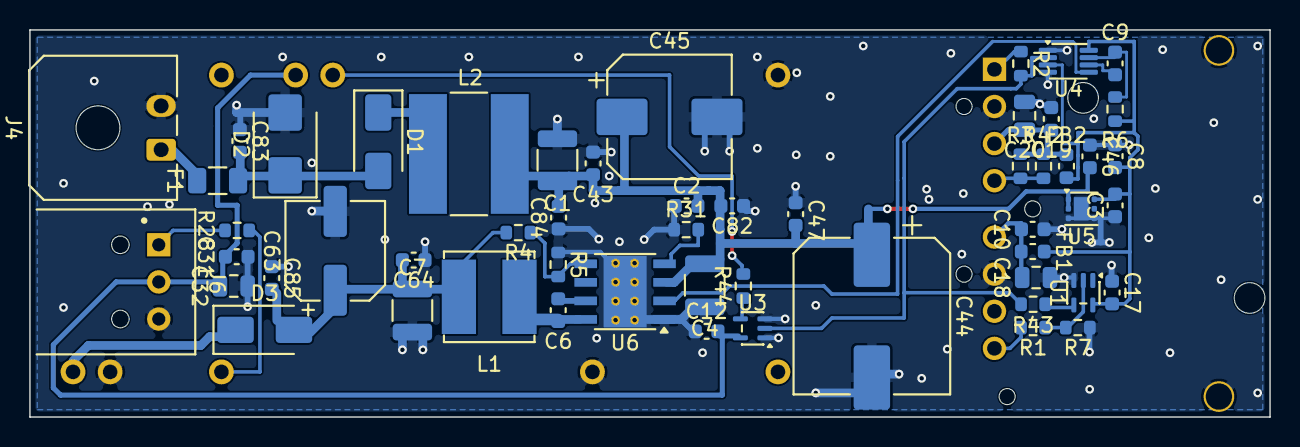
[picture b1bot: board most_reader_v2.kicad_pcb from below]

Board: 2 copper layers, 84.9 x 26.5 mm, 56 parts (54 on the bottom side), 28 nets.

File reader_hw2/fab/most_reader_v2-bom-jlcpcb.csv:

Comment,Designator,Footprint,LCSC Part #,Manufacturer Part
10u 100V,C1,C_1210_3225Metric,C576517,"Murata GRM32EC72A106KE05L, X7S"
100n 100V,"C2,C43,C46,C47,C82,C83,C84",C_0603_1608Metric,C15725,"Samsung CL10B104KC8NNNC, X7R"
2u2,C3,C_0603_1608Metric,C23630,"Samsung CL10A225KO8NNNC, 16 V X5R"
4u7 100V,C4,C_1210_3225Metric,C385986,"Taiyo Yuden HMK325C7475KMHPE, X7S"
100n,"C6,C8,C10,C12,C17,C19,C31,C64,C85",C_0603_1608Metric,C14663,"Yageo CC0603KRX7R9BB104, 50 V X7R"
47u 10V,C7,C_1210_3225Metric,C77101,"Murata GRM32ER61C476KE15L, 16 V X5R"
1u,C9,C_0603_1608Metric,C15849,"Samsung CL10A105KB8NNNC, 50 V X5R"
10u,"C18,C20",C_0805_2012Metric,C15850,"Samsung CL21A106KAYNNNE, 25 V X5R"
1u,C32,C_0805_2012Metric,C28323,"Samsung CL21B105KBFNNNE, 50 V X7R"
100u 63V,C44,CP_Elec_10x10.5,C53330124,"SamYoung CLZ 63V 100uF 10x10, 125 C"
47u 63V,C45,CP_Elec_8x10,C165628,"SamYoung MVK 63V 47uF 8x10, 105 C"
100u 16V,C63,CP_Elec_6.3x7.7,C359220,SamYoung BLA 16V 100uF 6.3x6
SS34,"D1,D3",D_SMA,C8678,MDD SS34
SMBJ36A,D2,D_SMB,C135070,Diodes SMBJ36A-13-F
2A T,F1,Fuse_1206_3216Metric,C2925010,"TLC F12T2, slow blow, 72 V"
600R,"FB1,FB2",L_0603_1608Metric,C1002,Sunlord GZ1608D601TF
15u,L1,L_Bourns_SRN6045TA,C1330797,Bourns SRN6045TA-150M
22u,L2,L_Bourns-SRN8040_8x8.15mm,C2041547,Bourns SRN8040-220M
150,"R1,R2",R_0603_1608Metric,C22808,UNI-ROYAL 0603WAF1500T5E
27k,"R3,R42",R_0603_1608Metric,C22967,UNI-ROYAL 0603WAF2702T5E
100k,"R4,R6,R7",R_0603_1608Metric,C25803,UNI-ROYAL 0603WAF1003T5E
23k2,R5,R_0603_1608Metric,C23346,UNI-ROYAL 0603WAF2322T5E
33,"R28,R43",R_0603_1608Metric,C23140,UNI-ROYAL 0603WAF330JT5E
64k9 1%,R31,R_0603_1608Metric,C14891,UNI-ROYAL 0603WAF6492T5E
68,R44,R_0603_1608Metric,C27592,UNI-ROYAL 0603WAF680JT5E
74LVC1G34,U1,SOT-353_SC-70-5,C353880,TI SN74LVC1G34DCKR
74LVC1G125,U3,SOT-353_SC-70-5,C7833,TI SN74LVC1G125DCKR
74LVC1G123,U4,VSSOP-8_2.3x2mm_P0.5mm,C352969,TI SN74LVC1G123DCUR
TPS7B8133DRV,U5,WSON-6-1EP_2x2mm_P0.65mm_EP1x1.6mm,C2876250,TI TPS7B8133DRVR
LMR38020F,U6,Texas_HSOP-8-1EP_3.9x4.9mm_P1.27mm_ThermalVias,C5149193,TI LMR38020FDDAR
